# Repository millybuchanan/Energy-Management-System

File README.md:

# Jetsurvey sample

Jetsurvey is a sample survey app, built with
[Jetpack Compose](https://developer.android.com/jetpack/compose). The goal of the sample is to
showcase text input, validation and state capabilities of Compose.

To try out this sample app, use the latest stable version
of [Android Studio](https://developer.android.com/studio).
You can clone this repository or import the
project from Android Studio following the steps
[here](https://developer.android.com/jetpack/compose/setup#sample).

## Features

This sample contains several screens: a welcome screen, where the user can enter their email, sign in and sign up screens and a survey screen. The app has light and dark themes.

### App scaffolding

Package [`com.example.compose.jetsurvey`][1]

[`MainActivity`][2] is the application's entry point. Each screen is implemented inside a `Fragment` and [`MainActivity`][2] is the host `Activity` for all of the `Fragment`s.
The navigation between them uses the [Navigation library][3]. The screens and the navigation are defined in [`Navigation.kt`][4]

[1]: app/src/main/java/com/example/compose/jetsurvey
[2]: app/src/main/java/com/example/compose/jetsurvey/MainActivity.kt
[3]: https://developer.android.com/guide/navigation
[4]: app/src/main/java/com/example/compose/jetsurvey/Navigation.kt

### Sign in/sign up

Package [`com.example.compose.jetsurvey.signinsignup`][5]

This package contains 3 screens:
* Welcome
* Sign in
* Sign up

To get to the sign up screen, enter an email that contains "signup".
These screens show how to create different custom composable functions, reused them across multiple screens and handle UI state.

See how to:

* Use `TextField`s
* Implement `TextField` validation across one `TextField` (e.g. email validation) and across multiple `TextFields` (e.g. password confirmation)
* Use a `Snackbar`
* Use different types of `Button`s: `TextButton`, `OutlinedButton` and `Button`

[5]: app/src/main/java/com/example/compose/jetsurvey/signinsignup

### Complete a survey

Package [`com.example.compose.jetsurvey.survey`][6]

This screen allows the user to fill out a survey, showing how to handle complex state. UI state is kept and restored on recompositions triggered by different reasons like a configuration change or a new question being displayed on the screen.

See how to:

* Use `RadioButton`s - for single item selection
* Use `Checkbox`es - for multi-item selection
* Use `Slider` - for picking a value from a range
* Use `Scaffold` - for screens with top bar, bottom bar and body
* Display a `DialogFragment` when requested from compose

[6]: app/src/main/java/com/example/compose/jetsurvey/survey

### Data

The data in the sample is static, held in the `*Repository` classes.

## Setup
The main [README](https://github.com/android/compose-samples/) has instructions on how to
setup this sample, and many others.

## License

```
Copyright 2020 The Android Open Source Project

Licensed under the Apache License, Version 2.0 (the "License");
you may not use this file except in compliance with the License.
You may obtain a copy of the License at

    https://www.apache.org/licenses/LICENSE-2.0

Unless required by applicable law or agreed to in writing, software
distributed under the License is distributed on an "AS IS" BASIS,
WITHOUT WARRANTIES OR CONDITIONS OF ANY KIND, either express or implied.
See the License for the specific language governing permissions and
limitations under the License.
```

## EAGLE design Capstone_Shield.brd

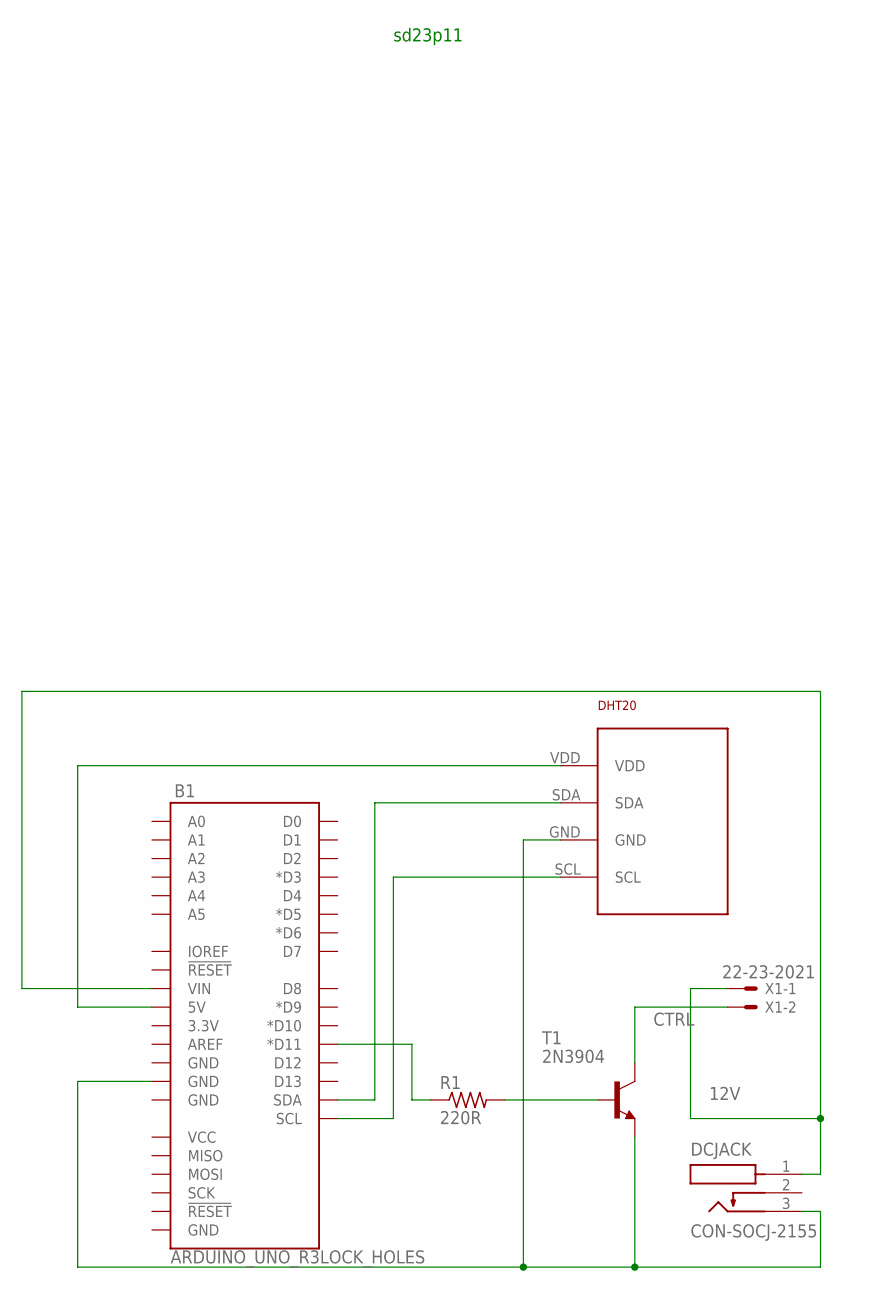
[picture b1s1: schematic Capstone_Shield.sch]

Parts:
B1: ARDUINO_UNO_R3LOCK_HOLES; ARDUINO_R3_LOCK_HOLES
DCJACK: CON-SOCJ-2155; GRAVITECH_CON-SOCJ-2155
R1: 220R; 0207/10
T1: 2N3904; TO92
U$1: DHT20THROUGH_HOLE; DHT20
X1: 22-23-2021; MPN FAN

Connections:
12V: B1.VIN, DCJACK.1, X1.1
CTRL: T1.1 (C), X1.2
unnamed: B1.5V, U$1.VDD
unnamed: B1.SDA, U$1.SDA
unnamed: B1.D11 (*D11), R1.1
unnamed: R1.2, T1.2 (B)
unnamed: B1.GND@3 (GND), DCJACK.3, T1.3 (E), U$1.GND
unnamed: B1.SCL, U$1.SCL

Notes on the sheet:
sd23p11

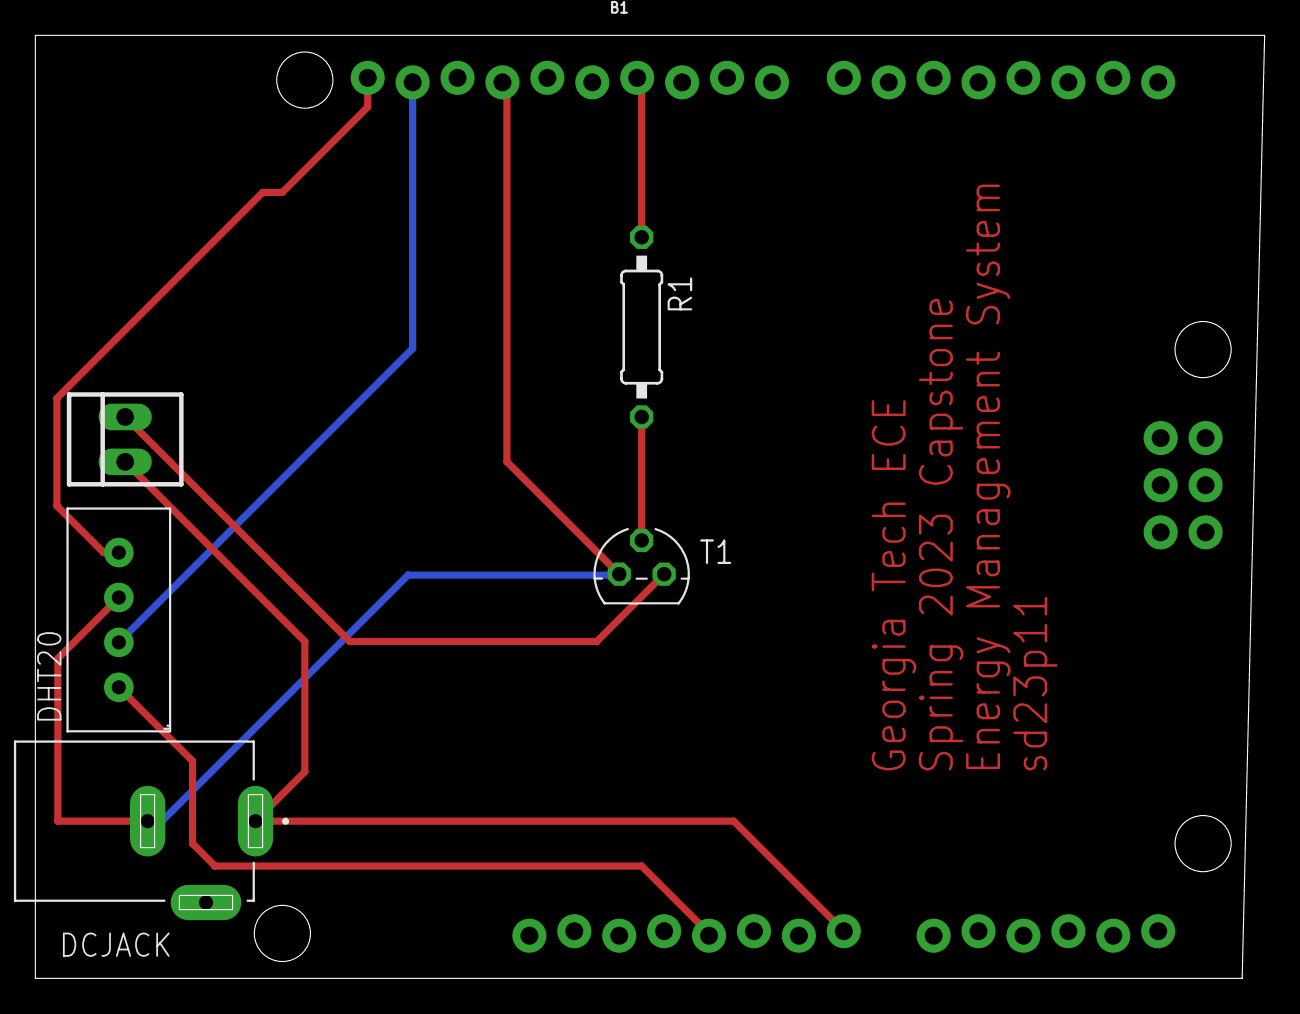
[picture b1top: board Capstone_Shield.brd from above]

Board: 2 copper layers, 69.5 x 53.3 mm, 6 parts (0 on the bottom side), 8 nets.

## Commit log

2023-02-17 Create algo.py
    Basic algorithm using simple linear regression
2023-02-20 Update algo.py
    Include user schedule as predictive variable
2023-03-15 added the question for "ideal brightness"
    flow should be correct but does not yet appear on the preview demo...
2023-03-15 made wireframes for brightness and temperature slider questions... not yet integrated with flow of app but they show a basic example of functionality for those particular screens
2023-03-15 got a working version of textfield input
    this is only the component to have a text field... need to integrate into the screen with question wrapper and jetsurvey theme
2023-03-15 work in progress: screen with 3 slider bars on the same screen to indicate priority of settings
    currently shows all three sliders on top of each other... will need to find some element that allows the sliders to be moved down on the page
2023-03-31 Added Dashboard and Preferences Screen
2023-03-31 Update Preferences.kt
    Make sure the title aligned in the middle of the screen
2023-03-31 Added Bottom navigation bar
    Need to fix routing: currently the app directly leads to main screen
2023-04-03 Fixed Navigation
    User is directed to dashboard after the survey
2023-04-05 Update SurveryNavigation.kt
    After signin, new user is directed to survey, and old user is directed to dashboard. Sign in as a guest is directed to the survey as well.
2023-04-05 current work in progress.. pushed to update the team
2023-04-05 Revert "current work in progress.. pushed to update the team"
    This reverts commit 604c5566c88e17a28b15387b9fd0efc4f114686d.
2023-04-05 Create profile_screen.kt
    start for profile screen
2023-04-05 Create feedback_screen.kt
    feedback screen for dashboard
2023-04-05 Integrate Profile and Feedback Screen to bottom navigation
2023-04-10 Updated fan test, humidity/temperature sensor test, as well as merging the two using threads.
2023-04-12 got age question working, survey components still need to be added
2023-04-12 Age Question Fixed for Survey
2023-04-12 got zipcode working, adding questionwrapper for title text
2023-04-12 Add title for age question
2023-04-12 Add title for zipcode question
2023-04-14 Revert "Hardware peripheral tests"
2023-04-14 April 14 Demo
    Small changes to individual peripheral tests, as well as completion of demo code for April 14. Please see README for my notes on this demo.
2023-04-14 Gender Question Fixed
2023-04-14 Brightness Question Fixed
2023-04-14 Add Temperature Questions
2023-04-18 Amplify Setup
2023-04-18 Fixed setting up Amplify
2023-04-18 Implement SignUp
2023-04-18 Implement Some SignUp Logic
    To do: Query the db to see if user exists correctly
2023-04-19 SignUp, SignIn Fully Functional
2023-04-19 Updated MainActivity
    Make sure Datastore is initialized before doing any operation on database
2023-04-19 Deleted Unused Survey Questions and Fixed Complete Survey Screen
2023-05-01 Upload all android studio code

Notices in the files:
parts and their libraries:
SparkFun-Boards: Licensing: Creative Commons ShareAlike 4.0 International - https://creativecommons.org/licenses/by-sa/4.0
